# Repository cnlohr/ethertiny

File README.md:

WARNING

This is a really dangerous project.  Use at your own risk.

By directly ethernet without magnetics to an AVR, you may
cause serious damage, fire, or anything else crazy if there
is a DC offset.  It does not follow 802.3 standards for
10Base-T Ethernet

It has two projects in it:
 t85: uses differential signaling with fixed packets, similar to another
	person's project, igorplug, found here:
	http://www.cesko.host.sk/IgorPlugUSB/IgorPlug-USB%20%28AVR%29_eng.htm

 t85spi: uses the USI, and can send/receive arbitrary packets.

Schematics are in the "hardware/" folder.

See the youtube video for more info:

T85 Video:    http://youtu.be/mwcvElQS-hM

T85spi Video: http://youtu.be/m4f4OzEyueg

Paper on T85spi is found in the "paper/" folder.

Copyright (C) 2014 <>< Charles Lohr

Permission is hereby granted, free of charge, to any person obtaining a
copy of this software and associated documentation files (the "Software"),
to deal in the Software without restriction, including without limitation
the rights to use, copy, modify, merge, publish, distribute, sublicense,
and/or sell copies of the Software, and to permit persons to whom the
Software is furnished to do so, subject to the following conditions:

The above copyright notice and this permission notice shall be included
in all copies or substantial portions of the Software.

THE SOFTWARE IS PROVIDED "AS IS", WITHOUT WARRANTY OF ANY KIND, EXPRESS
OR IMPLIED, INCLUDING BUT NOT LIMITED TO THE WARRANTIES OF
MERCHANTABILITY, FITNESS FOR A PARTICULAR PURPOSE AND NONINFRINGEMENT.
IN NO EVENT SHALL THE AUTHORS OR COPYRIGHT HOLDERS BE LIABLE FOR ANY
CLAIM, DAMAGES OR OTHER LIABILITY, WHETHER IN AN ACTION OF CONTRACT,
TORT OR OTHERWISE, ARISING FROM, OUT OF OR IN CONNECTION WITH THE
SOFTWARE OR THE USE OR OTHER DEALINGS IN THE SOFTWARE.

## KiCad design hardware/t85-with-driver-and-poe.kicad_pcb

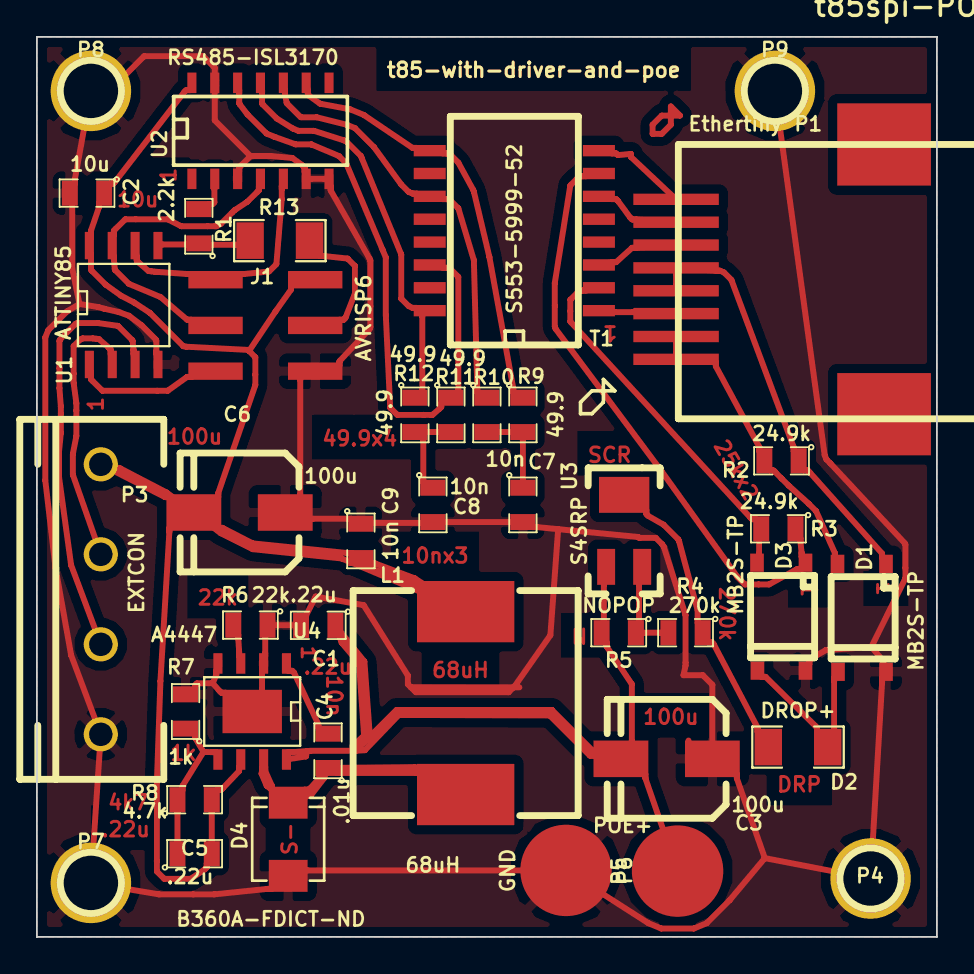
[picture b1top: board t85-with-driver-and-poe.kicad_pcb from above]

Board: 2 copper layers, 50.0 x 50.0 mm, 41 parts (0 on the bottom side), 32 nets.

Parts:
C1, C5: .22u; SM0805
C2: 10u; SM0805
C3, C6: 100u; PanasonicD8Cap
C4: .01u; SM0805
C7, C8, C9: 10n; SM0805
D1, D3: MB2S-TP; BESOP-4
D2: DROP+; SM1206
D4: B360A-FDICT-ND; DO_214AA
J1: AVRISP6; RIBBON6SMT
L1: 68uH; BOURNS-SRR1280
P1: Ethertiny; SMT_ETHERNET
P3: EXTCON; PHOENIX1935187
P4, P7, P8, P9: 632HOLE
P5: POE+; .2SMTPIN
P6: GND; .2SMTPIN
R1: 2.2k; SM0805
R2, R3: 24.9k; SM0805
R4: 270k; SM0805
R5: NOPOP; SM0805
R6: 22k; SM0805
R7: 1k; SM0805
R8: 4.7k; SM0805
R9, R10, R11, R12: 49.9; SM0805
R13: 0; SM1206
T1: S553-5999-52; BELFuse-S553
U1: ATTINY85; SO8WIDE
U2: RS485-ISL3170; SO14E
U3: S4SRP; DO-214AA
U4: A4447; SO8E-WITHPAD

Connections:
unnamed: C4.2, U4.1
unnamed: C1.1, C3.1, P5.1, R5.2, U3.1, U4.8
unnamed: D1.3, D2.2, D3.3
unnamed: R4.2, R5.1, U3.2
unnamed: D2.1, R4.1, U3.3
unnamed: C8.1, R11.2, R12.2
unnamed: C7.1, R9.2, R10.2
unnamed: J1.4, R13.1
unnamed: D1.2, P1.1, P1.2, R2.2
unnamed: C5.1, R7.1, R8.1, U4.5
unnamed: R6.2, U4.3
unnamed: C4.1, D4.2, L1.1, U4.7
unnamed: P3.2, U1.2
unnamed: R10.1, T1.11, U2.10
unnamed: R9.1, T1.9, U2.9
unnamed: P1.8, T1.8
unnamed: D3.1, R3.1, T1.7
unnamed: P1.6, T1.3
unnamed: D3.2, R3.2, T1.2
unnamed: J1.5, U1.1
unnamed: P3.3, U1.3
unnamed: R12.1, T1.16, U2.11
unnamed: P1.7, T1.6
unnamed: P1.3, T1.1
unnamed: R11.1, T1.14, U2.12
unnamed: D1.1, P1.4, P1.5, R2.1
unnamed: R1.1, R13.2, U1.5
unnamed: R1.2, U2.2
unnamed: J1.1, U1.6, U2.5
unnamed: J1.3, U1.7, U2.4
VCC: C2.1, C5.2, C6.1, C9.2, J1.2, L1.2, P3.1, R8.2, U1.8, U2.14, U4.6
VSS: C1.2, C2.2, C3.2, C6.2, C7.2, C8.2, C9.1, D1.4, D3.4, D4.1, J1.6, P3.4, P4.1, P6.1, P7.1, P8.1, P9.1, R6.1, R7.2, U1.4, U2.3, U2.6, U2.7, U2.13, U4.2, U4.4, U4.9

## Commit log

2014-08-28 add tin85 stuff
2014-08-29 add readme!
2014-08-29 fix formatting
2014-08-29 add warnings
2014-08-29 update with copyright info
2014-08-29 further notes
2014-08-29 tweak - add option for nop's... it doesn't help.
2014-08-30 first shot at SPI-style xmit.
2014-08-30 further progress toward a bi-directional ethernet device. Not sure if t's gonna be possible at all, but it's a fun try.
2014-08-30 add some files to clockrecovery - it's a rough high-level attempt at reconstructing the packet based on a high speed digital stream (~30MHz)
2014-08-30 Fixed a number of bugs, now accept packets on-wire and write their contens to the buffer and re-broadcast.
2014-08-31 progress with the histogram and tools
2014-08-31 Able to prase packets (on the PC)
2014-08-31 try to add and AVR-friendly demanchestration tool.
2014-08-31 Process incoming RX packets on the AVR
2014-08-31 remove clock recovery tool. It's wrong
2014-08-31 forgot to remove parsehelp
2014-08-31 oops!
2014-08-31 intermediate checkin...
2014-08-31 checkpoint 2.
2014-08-31 Another checkin. Get rid of the user having to handle the preamble noise
2014-08-31 add better readme
2014-08-31 forgot eth_config!
2014-08-31 Tweak - better preamble integration
2014-08-31 remoev test.lst it's just bulky
2014-08-31 still needs a great deal of work, but we are pinging.
2014-08-31 lower packet loss!
2014-08-31 Wlrelaxing
2014-08-31 progress.
2014-08-31 Add copyright notices.
2014-09-01 more cleanups. Let's mark this as a good go-to spot.
    *CHECKPOINT*
2014-09-01 hoorey! tweaks! Now we have ADC + WS2812
2014-09-01 add topside control, plus fix port #'s.
2014-09-02 tweak - even if a packet is incoming, read it anyway.
2014-09-02 Add "hict" and "loct" for debugging the bias system on the AVR. This also helps diagnose when soemthing's wrong and packets are coming in stunted.
2014-09-03 add a rough draft for the paper
2014-09-03 change comments
2014-09-04 down to a lower pcket loss + linking with switches a good clip away.
2014-09-04 furthe tweaks for reliability
2014-09-04 cleanup
2014-09-04 progress!!!
2014-09-04 Add in some schematics
2014-09-04 add schematic
2014-09-05 update paper
2014-09-05 forgot to update the broken diagram
2014-09-05 pretty big changes, make everything interrupt driven.
2014-09-05 tweaks to the control toolo
2014-09-05 fix orientation of pins
2014-09-05 oops needed to re-run latex
2014-09-05 add documentation + warnings
2014-09-05 fix readme
2015-04-11 update with the poe
2015-04-11 add a driver version... it doesn't seem to work off the bat, but we can work with it.
2024-10-08 Update PDF removing watermark

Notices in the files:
hardware/t85-with-driver-and-poe.kicad_pcb:
(C) 2014 C. Lohr
